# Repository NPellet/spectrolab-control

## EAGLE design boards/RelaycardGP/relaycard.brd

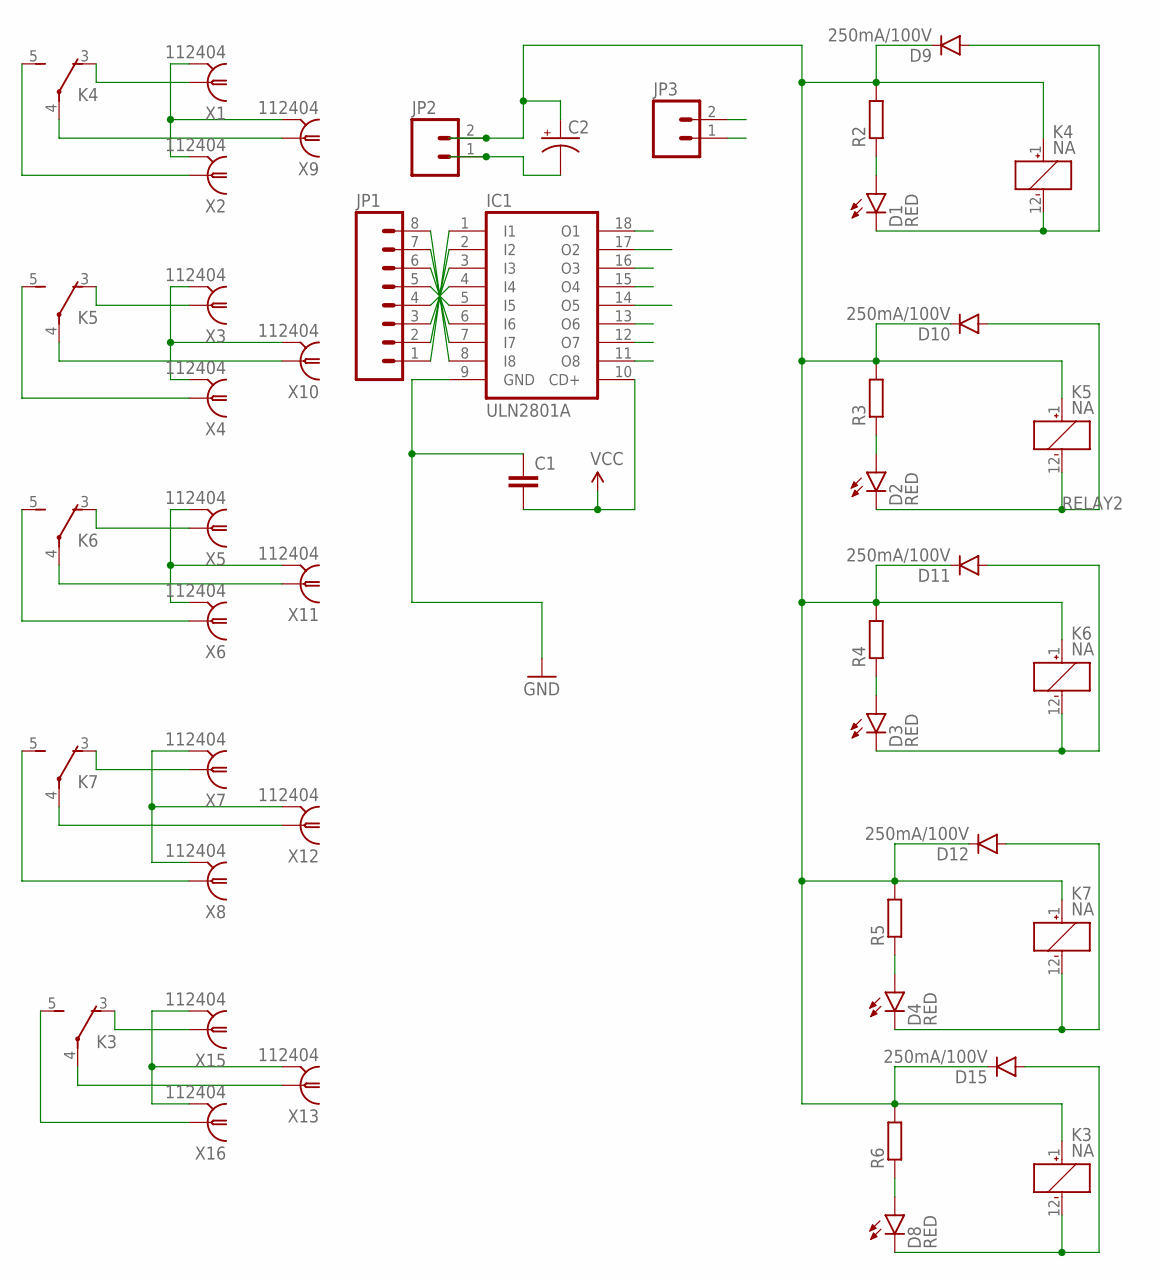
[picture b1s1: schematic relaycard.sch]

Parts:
C1: 0.1UF-50V-20%(PTH)KIT-EZ; CAP-PTH-SMALL-KIT
C2: 100UF-25V-20%(PTH); CPOL-RADIAL-100UF-25V
D1, D2, D3, D4, D8: RED; LED-1206
D9, D10, D11, D12, D15: 250mA/100V; SOD-323
IC1: ULN2801A; DIL18
JP1: M08; 1X08_ROUND
JP2, JP3: M02PTH; 1X02
K3, K4, K5, K6, K7: NA
R2, R3, R4, R5, R6: R-EU_R1206W; R1206W
X1, X2, X3, X4, X5, X6, X7, X8, X15, X16: 112404
X9, X10, X11, X12, X13: 112404; MPN 112404

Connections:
A: D1.A, R2.1
B: D2.A, R3.1
C: D3.A, R4.1
D: D4.A, R5.1
E: D8.A, R6.1
GND1: X1.2, X1.3 (2), X1.4 (2), X1.5 (2), X2.2, X2.3 (2), X2.4 (2), X2.5 (2), X9.2, X9.3 (2), X9.4 (2), X9.5 (2)
GND2: X3.2, X3.3 (2), X3.4 (2), X3.5 (2), X4.2, X4.3 (2), X4.4 (2), X4.5 (2), X10.2, X10.3 (2), X10.4 (2), X10.5 (2)
GND3: X5.2, X5.3 (2), X5.4 (2), X5.5 (2), X6.2, X6.3 (2), X6.4 (2), X6.5 (2), X11.2, X11.3 (2), X11.4 (2), X11.5 (2)
GND4: X7.2, X7.3 (2), X7.4 (2), X7.5 (2), X8.2, X8.3 (2), X8.4 (2), X8.5 (2), X12.2, X12.3 (2), X12.4 (2), X12.5 (2)
GND5: X13.2, X13.3 (2), X13.4 (2), X13.5 (2), X15.2, X15.3 (2), X15.4 (2), X15.5 (2), X16.2, X16.3 (2), X16.4 (2), X16.5 (2)
GND_V: C1.1, C2.2 (-), IC1.9 (GND), JP2.1, JP3.1, JP3.2
unnamed: K4.5 (S), X2.1
unnamed: IC1.1 (I1), JP1.1
unnamed: K4.3 (O), X1.1
unnamed: K4.4, X9.1
unnamed: K5.5 (S), X4.1
unnamed: IC1.2 (I2), JP1.2
unnamed: K5.3 (O), X3.1
unnamed: IC1.3 (I3), JP1.3
unnamed: IC1.4 (I4), JP1.4
unnamed: IC1.5 (I5), JP1.5
unnamed: IC1.6 (I6), JP1.6
unnamed: IC1.7 (I7), JP1.7
unnamed: K5.4, X10.1
unnamed: K6.3 (O), X5.1
unnamed: K6.5 (S), X6.1
unnamed: K6.4, X11.1
unnamed: K7.3 (O), X7.1
unnamed: IC1.8 (I8), JP1.8
unnamed: K7.5 (S), X8.1
unnamed: K7.4, X12.1
unnamed: K3.3 (O), X15.1
unnamed: K3.5 (S), X16.1
unnamed: K3.4, X13.1
RELAY1: D1.C, D9.A, IC1.17 (O2), K4.12 (-)
RELAY2: D2.C, D10.A, IC1.16 (O3), K5.12 (-)
RELAY3: D3.C, D11.A, IC1.15 (O4), K6.12 (-)
RELAY4: D4.C, D12.A, IC1.14 (O5), K7.12 (-)
RELAY5: D8.C, D15.A, IC1.18 (O1), K3.12 (-)
RELAY6: IC1.13 (O6)
RELAY7: IC1.12 (O7)
RELAY8: IC1.11 (O8)
VCC: C1.2, C2.1 (+), D9.C, D10.C, D11.C, D12.C, D15.C, IC1.10 (CD+), JP2.2, K3.1 (+), K4.1 (+), K5.1 (+), K6.1 (+), K7.1 (+), R2.2, R3.2, R4.2, R5.2, R6.2

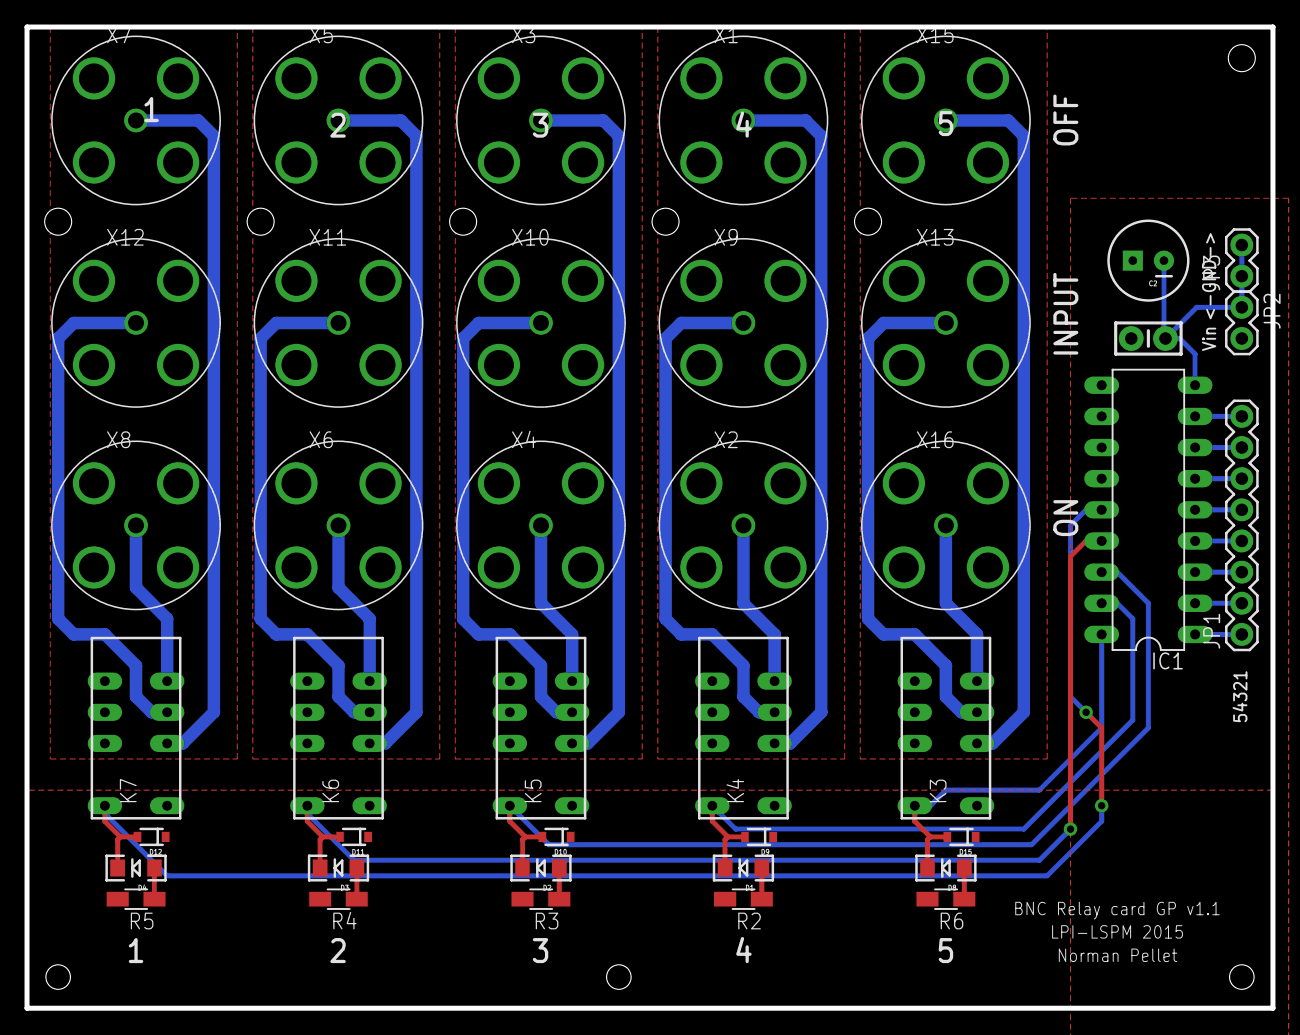
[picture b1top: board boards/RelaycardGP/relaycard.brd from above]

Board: 2 copper layers, 101.6 x 80.0 mm, 41 parts (0 on the bottom side), 40 nets.

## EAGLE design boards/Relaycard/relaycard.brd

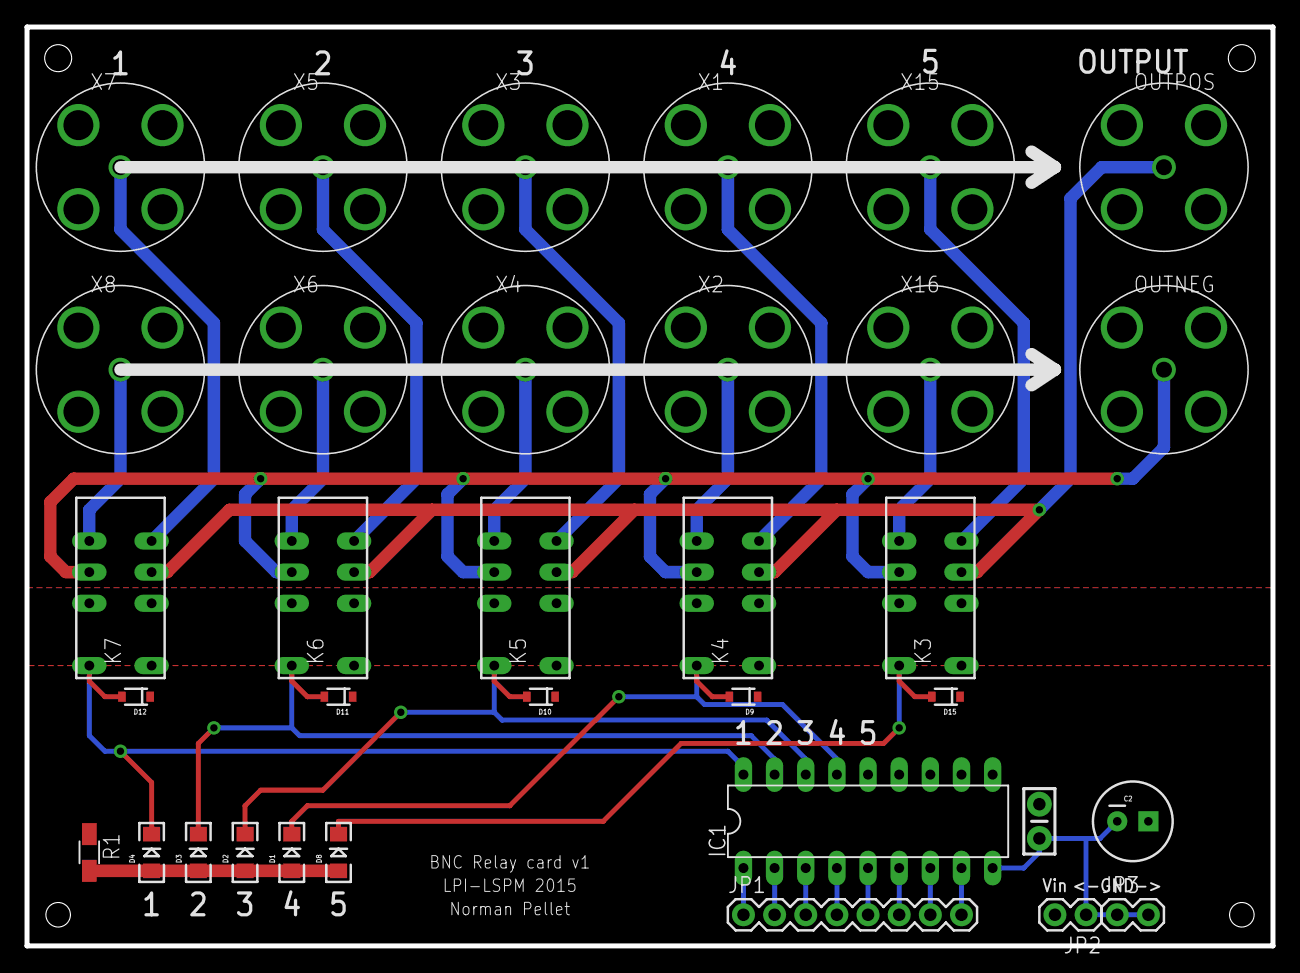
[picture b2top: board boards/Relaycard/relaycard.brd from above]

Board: 2 copper layers, 101.6 x 74.9 mm, 34 parts (0 on the bottom side), 29 nets.

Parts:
C1: CAP-PTH-SMALL-KIT
C2: CPOL-RADIAL-100UF-25V
D1, D2, D3, D4, D8: RED; LED-1206
D9, D10, D11, D12, D15: 250mA/100V; SOD-323
IC1: ULN2801A; DIL18
JP1: 1X08_ROUND
JP2, JP3: 1X02
K3, K4, K5, K6, K7: NA
OUTNEG: 112404
OUTPOS: 112404
R1: R1206W
X1, X2, X3, X4, X5, X6, X7, X8, X15, X16: 112404

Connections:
GND: OUTNEG.2, OUTNEG.3, OUTNEG.4, OUTNEG.5, OUTPOS.2, OUTPOS.3, OUTPOS.4, OUTPOS.5, X1.2, X1.3, X1.4, X1.5, X2.2, X2.3, X2.4, X2.5, X3.2, X3.3, X3.4, X3.5, X4.2, X4.3, X4.4, X4.5, X5.2, X5.3, X5.4, X5.5, X6.2, X6.3, X6.4, X6.5, X7.2, X7.3, X7.4, X7.5, X8.2, X8.3, X8.4, X8.5, X15.2, X15.3, X15.4, X15.5, X16.2, X16.3, X16.4, X16.5
GND2: C1.1, C2.2, IC1.9, JP2.1, JP3.1, JP3.2
unnamed: K4.5, X1.1
unnamed: IC1.1, JP1.1
unnamed: K4.8, X2.1
unnamed: K5.5, X3.1
unnamed: K5.8, X4.1
unnamed: IC1.2, JP1.2
unnamed: K6.5, X5.1
unnamed: IC1.3, JP1.3
unnamed: IC1.4, JP1.4
unnamed: IC1.5, JP1.5
unnamed: IC1.6, JP1.6
unnamed: IC1.7, JP1.7
unnamed: K6.8, X6.1
unnamed: IC1.8, JP1.8
unnamed: K7.5, X7.1
unnamed: K7.8, X8.1
unnamed: K3.5, X15.1
unnamed: K3.8, X16.1
OUTNEG: K3.9, K4.9, K5.9, K6.9, K7.9, OUTNEG.1
OUTPOS: K3.4, K4.4, K5.4, K6.4, K7.4, OUTPOS.1
RELAY1: D4.C, D12.A, IC1.18, K7.12
RELAY2: D3.C, D11.A, IC1.17, K6.12
RELAY3: D2.C, D10.A, IC1.16, K5.12
RELAY4: D1.C, D9.A, IC1.15, K4.12
RELAY5: D8.C, D15.A, IC1.14, K3.12
RES: D1.A, D2.A, D3.A, D4.A, D8.A, R1.2
VCC: C1.2, C2.1, D9.C, D10.C, D11.C, D12.C, D15.C, IC1.10, JP2.2, K3.1, K4.1, K5.1, K6.1, K7.1, R1.1

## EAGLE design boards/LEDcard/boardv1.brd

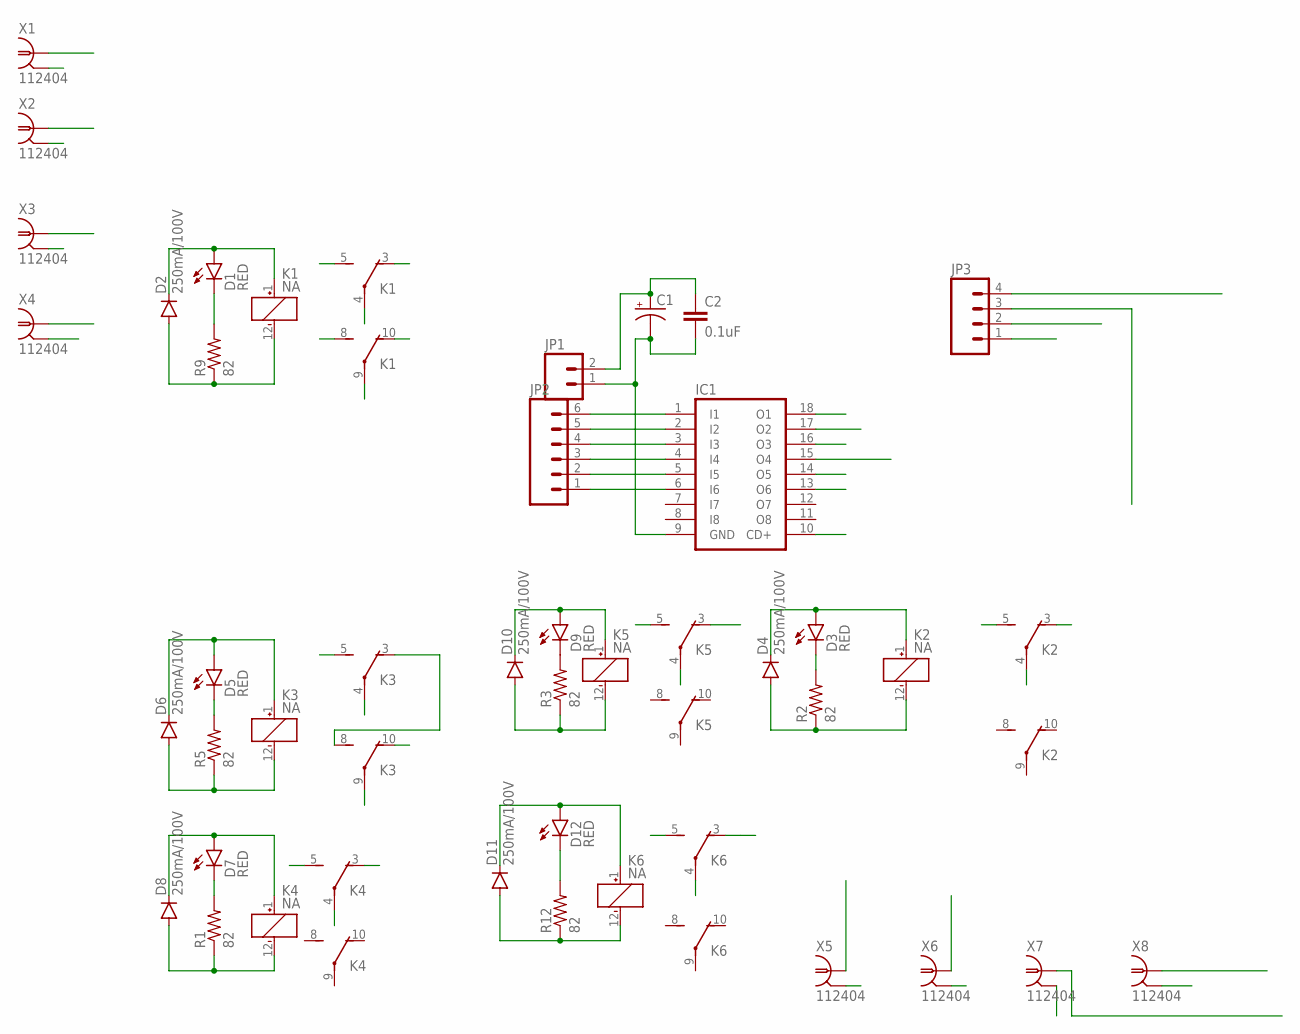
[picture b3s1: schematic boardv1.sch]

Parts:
C1: 100UF-25V-20%(PTH); CPOL-RADIAL-100UF-25V
C2: 0.1uF; 0603-CAP
D1, D3, D5, D7, D9, D12: RED; LED-1206
D2, D4, D6, D8, D10, D11: 250mA/100V; SOD-323
IC1: ULN2803A; DIL18
JP1: M02PTH; 1X02
JP2: M06NO_SILK_YES_STOP; 1X06_NO_SILK_YES_STOP
JP3: M04PTH; 1X04
K1, K2, K3, K4, K5, K6: NA
R1, R2, R3, R5, R9, R12: 82; 0603-RES
X1, X2, X3, X4, X5, X6, X7, X8: 112404

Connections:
ARDUINO1: JP3.4, K2.3 (O)
ARDUINO2: JP3.3, K6.3 (O)
ARDUINO3: JP3.2, K5.3 (O)
ARDUINO4: JP3.1, K4.3 (O)
GND: X1.2, X1.3 (2), X1.4 (2), X1.5 (2), X2.2, X2.3 (2), X2.4 (2), X2.5 (2), X3.2, X3.3 (2), X3.4 (2), X3.5 (2), X4.2, X4.3 (2), X4.4 (2), X4.5 (2), X5.2, X5.3 (2), X5.4 (2), X5.5 (2), X6.2, X6.3 (2), X6.4 (2), X6.5 (2), X7.2, X7.3 (2), X7.4 (2), X7.5 (2), X8.2, X8.3 (2), X8.4 (2), X8.5 (2)
GND2: C1.2 (-), C2.2, IC1.9 (GND), JP1.1
INPUTA: K1.4, X1.1
INPUTB: K1.9, X2.1
unnamed: D1.C, R9.2
unnamed: D12.C, R12.2
unnamed: D5.C, R5.2
unnamed: D9.C, R3.2
unnamed: D7.C, R1.2
unnamed: IC1.6 (I6), JP2.1
unnamed: IC1.1 (I1), JP2.6
unnamed: IC1.2 (I2), JP2.5
unnamed: IC1.3 (I3), JP2.4
unnamed: D3.C, R2.2
unnamed: IC1.4 (I4), JP2.3
unnamed: IC1.5 (I5), JP2.2
OUTPUT1: K4.4, X5.1
OUTPUT2: K5.4, X6.1
OUTPUT3: K6.4, X7.1
OUTPUT4: K2.4, X8.1
OUTPUTA: K1.3 (O), K3.5 (S), X3.1
OUTPUTB: K1.10 (O), K3.10 (O), X4.1
R1: D4.A, IC1.18 (O1), K2.12 (-), R2.1
R2: D11.A, IC1.17 (O2), K6.12 (-), R12.1
R3: D10.A, IC1.16 (O3), K5.12 (-), R3.1
R4: D8.A, IC1.15 (O4), K4.12 (-), R1.1
R5: D6.A, IC1.14 (O5), K3.12 (-), R5.1
R6: D2.A, IC1.13 (O6), K1.12 (-), R9.1
SIG3A: K1.5 (S), K3.4
SIG3B: K1.8 (S), K3.9
SIG4A: K2.5 (S), K3.3 (O), K3.8 (S), K4.5 (S), K5.5 (S), K6.5 (S)
VCC: C1.1 (+), C2.1, D1.A, D2.C, D3.A, D4.C, D5.A, D6.C, D7.A, D8.C, D9.A, D10.C, D11.C, D12.A, IC1.10 (CD+), JP1.2, K1.1 (+), K2.1 (+), K3.1 (+), K4.1 (+), K5.1 (+), K6.1 (+)

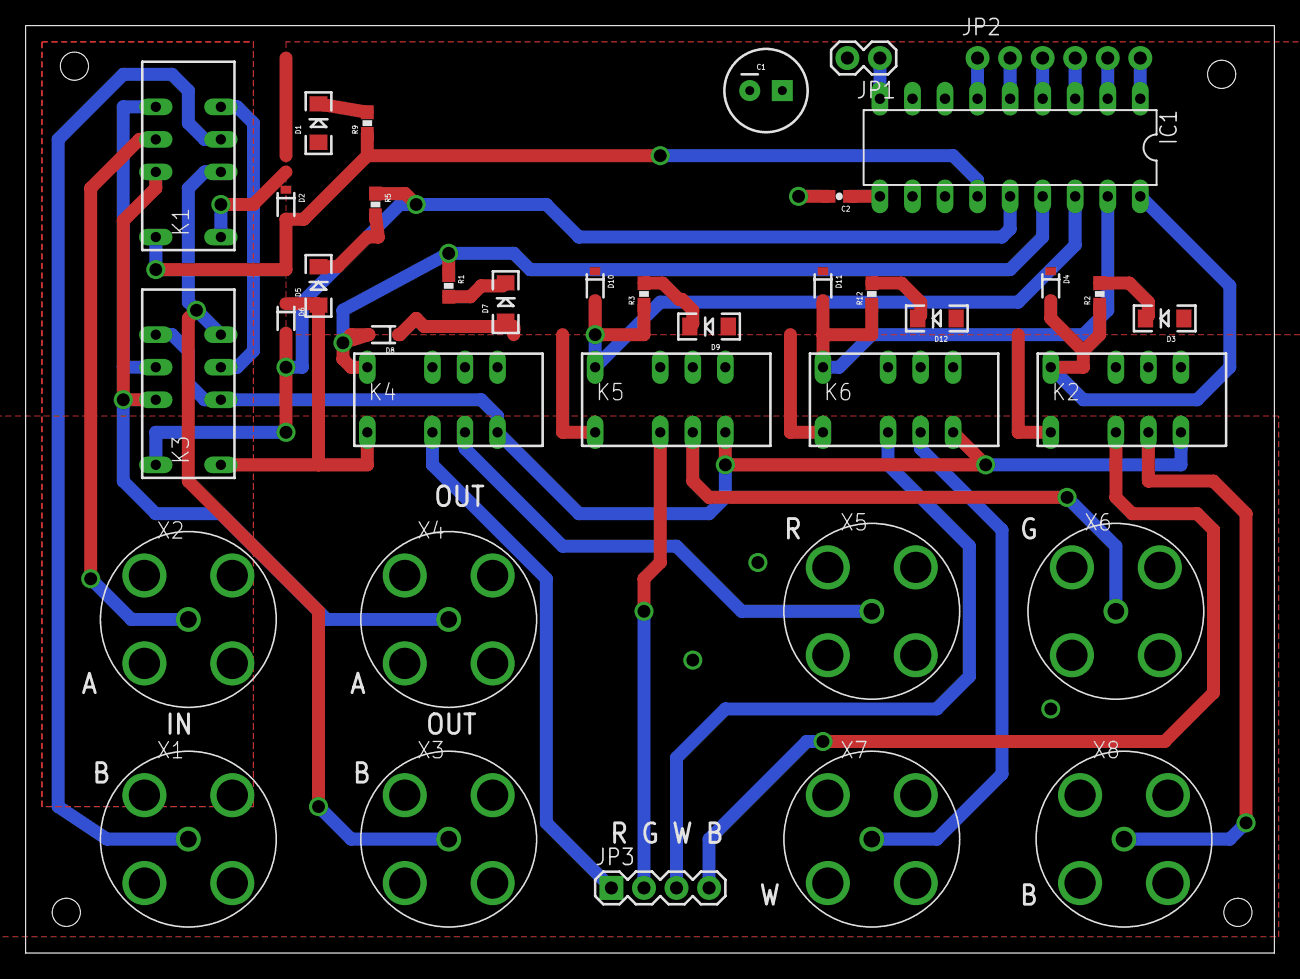
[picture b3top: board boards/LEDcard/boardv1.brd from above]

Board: 2 copper layers, 97.5 x 72.4 mm, 38 parts (0 on the bottom side), 36 nets.

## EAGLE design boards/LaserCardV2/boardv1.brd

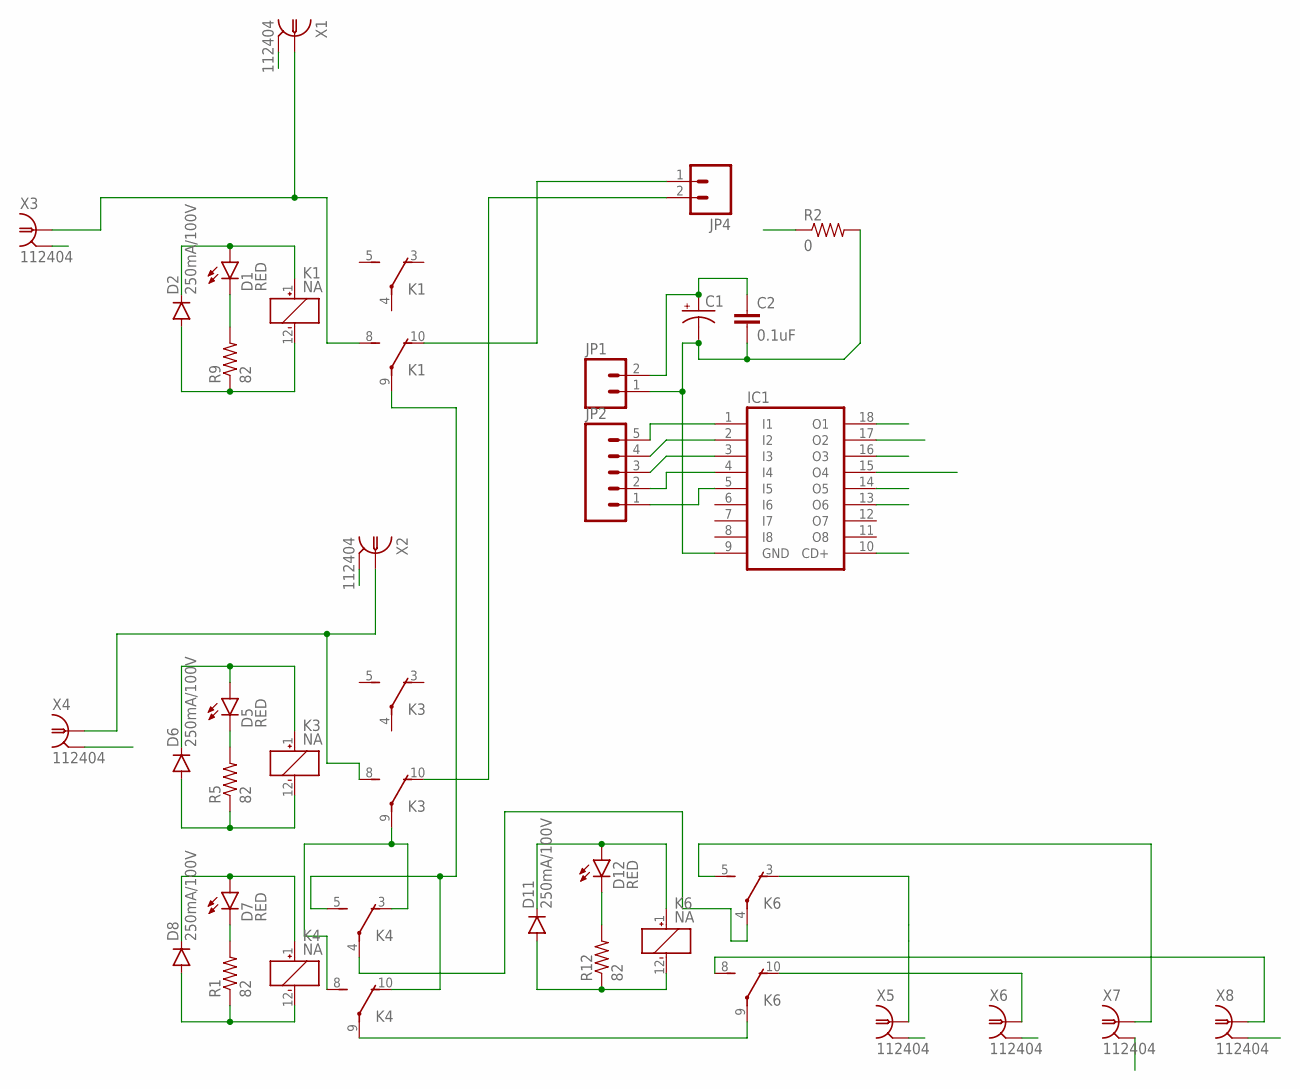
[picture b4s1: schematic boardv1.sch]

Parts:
C1: 100UF-25V-20%(PTH); CPOL-RADIAL-100UF-25V
C2: 0.1uF; 0603-CAP
D1, D5, D7, D12: RED; LED-1206
D2, D6, D8, D11: 250mA/100V; SOD-323
IC1: ULN2803A; DIL18
JP1, JP4: M02PTH; 1X02
JP2: M05PTH; 1X05
K1, K3, K4, K6: NA
R1, R5, R9, R12: 82; 0603-RES
R2: 0; 0603
X1, X2, X3, X4, X5, X6, X7, X8: 112404

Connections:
ANALOG: K4.9, K6.9
ARDUINO1: JP4.2, K3.10 (O), K4.3 (O)
DIGITAL: K4.4, K6.4
GND: R2.1, X1.2, X1.3 (2), X1.4 (2), X1.5 (2), X2.2, X2.3 (2), X2.4 (2), X2.5 (2), X3.2, X3.3 (2), X3.4 (2), X3.5 (2), X4.2, X4.3 (2), X4.4 (2), X4.5 (2), X5.2, X5.3 (2), X5.4 (2), X5.5 (2), X6.2, X6.3 (2), X6.4 (2), X6.5 (2), X7.2, X7.3 (2), X7.4 (2), X7.5 (2), X8.2, X8.3 (2), X8.4 (2), X8.5 (2)
GND2: C1.2 (-), C2.2, IC1.9 (GND), JP1.1, R2.2
unnamed: JP4.1, K1.10 (O)
unnamed: D1.C, R9.2
unnamed: D12.C, R12.2
unnamed: D5.C, R5.2
unnamed: D7.C, R1.2
unnamed: IC1.1 (I1), JP2.5
unnamed: IC1.2 (I2), JP2.4
unnamed: IC1.3 (I3), JP2.3
unnamed: IC1.4 (I4), JP2.2
unnamed: IC1.5 (I5), JP2.1
O1: K1.9, K4.5 (S), K4.10 (O)
O2: K3.8 (S), X2.1, X4.1
OUTPUT1: K6.3 (O), X5.1
OUTPUT2: K6.10 (O), X6.1
OUTPUT4: K6.8 (S), X8.1
OUTPUTA: K1.8 (S), X1.1, X3.1
R1: D11.A, IC1.18 (O1), K6.12 (-), R12.1
R2: D8.A, IC1.17 (O2), K4.12 (-), R1.1
R3: D6.A, IC1.16 (O3), K3.12 (-), R5.1
R4: D2.A, IC1.15 (O4), K1.12 (-), R9.1
R5: IC1.14 (O5)
R6: IC1.13 (O6)
SIG3B: K3.9, K4.8 (S)
SIG4A: K6.5 (S), X7.1
VCC: C1.1 (+), C2.1, D1.A, D2.C, D5.A, D6.C, D7.A, D8.C, D11.C, D12.A, IC1.10 (CD+), JP1.2, K1.1 (+), K3.1 (+), K4.1 (+), K6.1 (+)

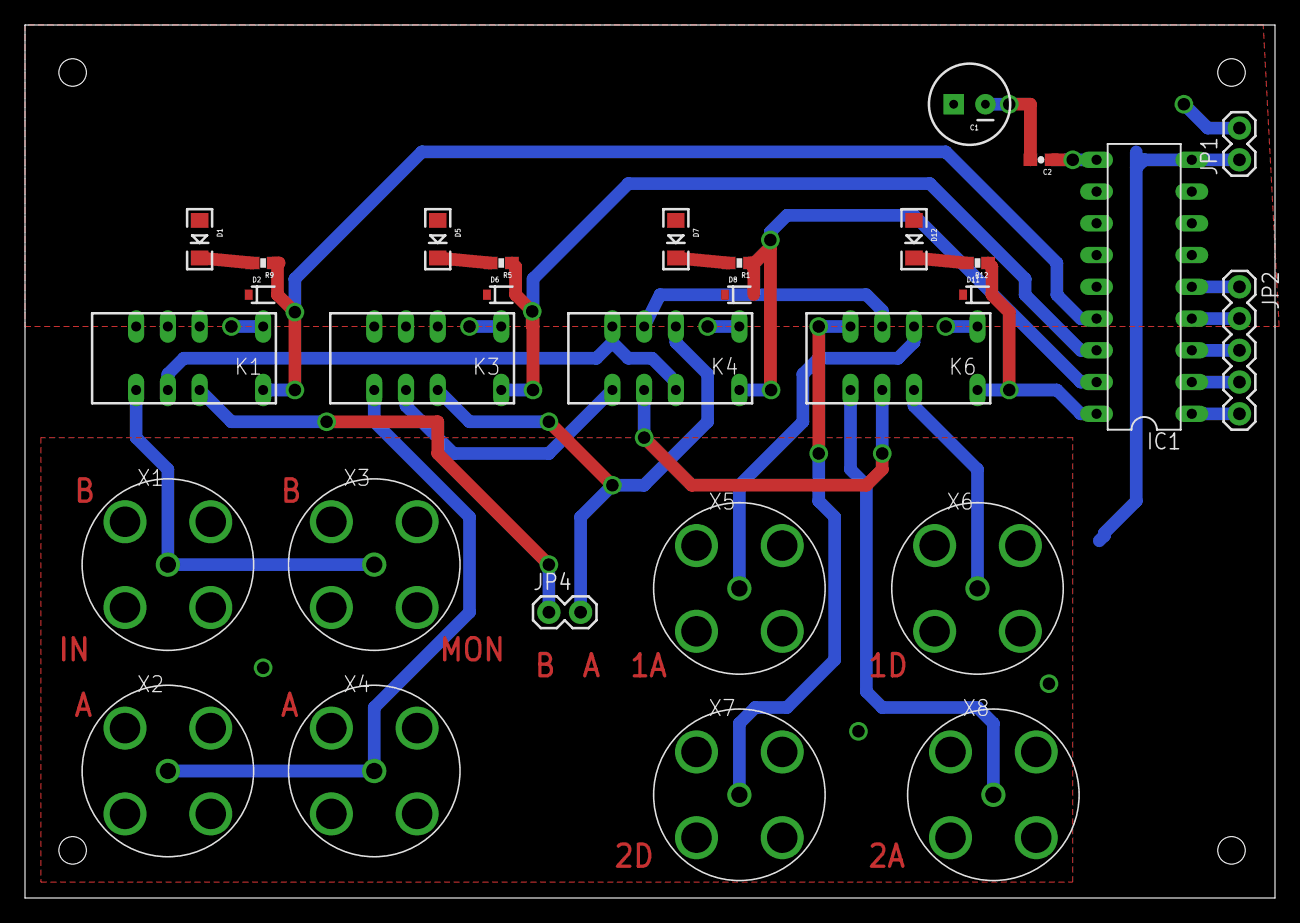
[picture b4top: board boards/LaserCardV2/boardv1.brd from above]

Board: 2 copper layers, 100.0 x 69.8 mm, 31 parts (1 on the bottom side), 28 nets.

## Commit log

2014-11-14 Project starting
2014-11-14 Start debugging
2014-11-14 Continue debugging
2014-11-17 Run keithley correctly
2014-11-17 Add keithley sweeping and jsGraph
2014-11-18 Update exps
2014-11-18 Update biascontrol
2014-11-24 igor saver and file info and bias update
2014-12-02 Update structure
2014-12-02 Start the python vxi11 control setup
2014-12-02 First communication with Tektronix scope
2014-12-02 Getting a wave out of the scope !
2014-12-04 Fix many bugs, add legend
2014-12-04 Change the communication system
2014-12-04 Module JS and CSS to be printed from memory and scss
2014-12-05 Allows single connection - bad design
2015-02-09 Update all
2015-02-10 Update experiment
2015-02-10 Improve capacitance timebase rejection filter
2015-02-10 Attempt to improve capacitance measurement filters
2015-02-10 Fix generator bugs and fix experiment
2015-02-10 Refactoring to prepare for multiple connections
2015-02-11 Allow multiple connection and upgrade client side
2015-02-11 Improve gould connect module
2015-02-11 Problem ?
2015-02-11 Fix graphs and keithley connect
2015-02-11 Open to public ip
2015-02-11 Update status
2015-02-11 Fix eDecayCapacitance renderer
2015-02-11 Fix wraper unref
2015-02-11 Fix status module
2015-02-11 Fix eDecayCapa rendering
2015-02-11 Default status
2015-02-11 VocDecay - First draft
2015-02-11 Allow advanced concat
2015-02-11 Update VocDecay experiment + Upgrade waveform util
2015-02-11 Start arduino
2015-02-11 Add Arduino support
2015-02-11 Add light intensities in eDecayCapa
2015-02-11 Fix eDecay Capacitance procedure
2015-02-11 Update eDecayCapa
2015-02-11 Update some styling
2015-02-11 Sass compiles unscoped module scss into scoped one
2015-02-12 Prepare AFG support
2015-02-12 Update AFG communication
2015-02-13 Update project
2015-02-13 Conflict ?
2015-02-16 First draft of Voc Decay experiment
2015-02-16 CELIV
2015-02-16 Add possibility to use shortcuts for renderer
2015-02-16 arduino update
2015-02-17 Update experiment definitions
2015-02-17 Resolve conflicts
2015-02-17 Update eps
2015-02-18 Update controller
2015-02-20 Alpaca
2015-02-23 Update experiments
2015-02-26 Update capacitance experiment
2015-03-03 Update FTDI
2015-03-09 TLTD
2015-03-13 Experiments update and Tektronix Scope imply
2015-03-14 Update tektronix API
2015-03-14 Update exp
2015-03-14 Fix tektronix getWave
2015-03-14 Get channel
2015-03-14 Fix controller
2015-03-14 Controller
2015-03-14 default waveform scaling
2015-03-14 Improve API
2015-03-14 Fix example
2015-03-14 Fix API
2015-03-14 test API
2015-03-14 API fix
2015-03-14 fix regex
2015-03-14 typo
2015-03-14 Log more for debug
2015-03-14 API Update
2015-03-20 Update experiments w/ Tk Scope
2015-04-01 more progress.
2015-04-08 Update small perturbation
2015-04-10 remove alpaca
2015-05-18 Start changing experiments
2015-05-18 update arduino
2015-05-20 Fix IV
2015-05-27 Update Q Extr
2015-05-28 Update QExtr Voc
2015-05-28 Update device experiments
2015-06-01 Fix current interrupt and qextraction jsc
2015-06-02 Update proc
2015-06-03 TPCTPV
2015-06-12 Update procedures
2015-06-12 update loader
2015-07-27 Instrument update
2015-07-27 Update all that shit
2015-07-27 update node
2015-07-27 Update PWS
2015-07-28 Prepare OBIS
2015-07-31 Update serial communication with Arduino
2015-07-31 Update IO and graph
2015-08-06 Add arduino controller
2015-08-06 Update node modules
2015-08-14 Fix Keithley
2015-09-26 Update scripts
2015-09-28 New structure
2015-09-28 Last changes
2015-10-01 Update CSS
2015-10-01 Board update
2015-10-01 Node modules
2015-10-01 All node modules
2015-10-01 All files fix
2015-10-01 Latest sun calibration method
2015-10-02 Update TPV
2015-10-03 Update TPV and QExtr procedures
2015-10-03 New instrument controller version
2015-10-03 Not sure where the problem is
2015-10-03 Last fix attemps
2015-10-06 Update frontend + connection via python
2015-10-12 Update on Keithley procedure
2015-10-14 Q extraction jsc
2015-10-15 Fix procedures
2015-10-22 Allow to remove methods
2015-10-23 Update config for relay pins

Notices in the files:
parts and their libraries:
SparkFun-LED: Licensing: Creative Commons ShareAlike 4.0 International - https://creativecommons.org/licenses/by-sa/4.0
